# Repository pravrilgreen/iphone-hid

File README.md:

# iphone-hid

**Remote touch, keyboard and screen for real iPhones.** One small box per phone. People use it from
a browser; test frameworks use its HTTP API or the Python SDK.

**Demo videos:** [the console through every state](docs/media/console-demo.mp4) (2 min: touch, typing, the
phone's buttons, a test script running, the cable unplugged, the phone asleep, the picture lost, a
second operator, the box going away) and [on a phone](docs/media/console-demo-mobile.mp4) (20 s).
Recorded against the simulated iPhone with `make demo`.

## What it does

- **Live screen** in the browser, cut to the phone, at the phone's frame rate.
- **Touch as it happens.** Click to tap, drag to swipe or move things, scroll with the wheel, hold for
  a long press. The box drives the iPhone's absolute pointer, so every touch lands where it was made.
- **Keyboard.** Type straight onto the phone, or paste text (printable ASCII).
- **Phone buttons.** Home, App Switcher, Search, volume, mute, play/pause, and wake.
- **Automation.** A REST API with an OpenAPI description, a WebSocket for live control, a Python SDK
  and the `ihc` command. Boxes announce themselves on the local network.
- **One file to install.** A 3.4 MB self-installing bundle for ARM64 boards.

## How it works

- **Touch and keys.** The board's USB-C port runs as a USB device: an absolute pointer whose range
  covers the whole screen, a keyboard, and media keys. iOS shows the pointer through AssistiveTouch.
  The box sends each report as soon as the input arrives. While a report waits for the iPhone to
  collect it, newer moves replace the waiting one, so the pointer follows the hand without a queue;
  presses and releases always keep their order.
- **Screen.** The iPhone mirrors its screen over HDMI into the board's HDMI input. The box cuts the
  phone out of each 1080p frame, encodes it as JPEG with libjpeg-turbo, and sends it to each viewer
  as soon as the viewer has drawn the previous one.
- **Software.** `ihcd`, one static Go binary: the API, the console, the USB gadget set-up and the
  video capture.

## Performance

| Path | Measured | Where |
|---|---|---|
| Touch on the box: from the input arriving to its report queued on the USB port | under 0.1 ms typical, 0.3 ms at worst | `ihcd`, simulated iPhone, development machine |
| The iPhone collecting a queued report | 2.6 ms | Orange Pi 5 Plus and iPhone 15, earlier box software |
| JPEG encoding of the phone screen (498 × 1080) | 3.0 ms per frame | development machine (x86-64); not yet measured on the board |

A scripted tap takes about 260 ms by design: the pointer settles for 80 ms after a jump, the press
lasts 80 ms, then the releases. The picture runs at the iPhone's mirror rate, up to 60 fps with the
box's 1080p60 EDID; the glass-to-glass video latency on the board is not measured yet. On each box,
the console's top bar shows the touch latency, the picture rate and age, and the network round trip,
live.

## Status

- **On a real iPhone:** the box's USB gadget and its absolute pointer were confirmed on an iPhone 15
  with the earlier box software (iOS version not recorded). `ihcd` sets up the same gadget; its run
  through the [hardware check](docs/guide/hardware-check.md) on a board is pending, and its results
  will be published in `docs/test-logs/`.
- **Everything else** (the console, the API, the SDK, the touch engine, the fault states) is tested
  against the simulated iPhone, in CI and in the demo videos.
- **Pre-release:** versions 0.x are pre-releases, not yet tested as a whole on real hardware; the
  API may still change before 1.0. Changes are listed in the [changelog](CHANGELOG.md).

## Limits

- One pointer: taps, drags, swipes, long presses and the wheel. No pinch or other multi-touch.
- Typing takes printable ASCII on the U.S. hardware keyboard layout; other text is refused, not
  mistyped.
- The AssistiveTouch pointer shows on the screen, and so in screenshots.
- Apps that protect their content (DRM video) show black over HDMI.
- The box works as a person with a mouse and keyboard would: it does not install apps, read logs or
  inspect the UI tree.

## Security

- Every call except `/api/health` needs the box's token, a random string in `/var/lib/ihc/token`
  that only the service can read. WebSockets and image URLs pass it as `?token=`.
- The box serves plain HTTP on port 8000 of every interface. Keep boxes on a network of their own,
  or serve HTTPS (`--tls-cert`, `--tls-key`) and bind one interface (`--addr`): see
  [install](docs/guide/install.md#network-and-security).
- Pages of other origins are refused, and so are host names the box does not know (DNS names need
  `--allow-host`).
- Whoever has the token drives the phone like a person holding it; with the phone's passcode off,
  guard the token like the phone. Report vulnerabilities as [SECURITY.md](SECURITY.md) says.

## What each box needs

| Part | Notes |
|---|---|
| Orange Pi 5 Plus and its 5 V / 4 A supply | Runs the box: USB device port, HDMI input, network |
| USB-C hub with HDMI, USB-A and a USB-C PD charging input | HDMI through DisplayPort Alt Mode, e.g. UGREEN Revodok 105 (15495) |
| USB-C charger, 30 W or more | Into the hub's PD input: powers the hub, charges the phone |
| HDMI cable | Hub to the board's HDMI IN |
| USB-A to USB-C cable (data) | Hub's USB-A to the board's Type-C USB 3 port |
| Ethernet | API and console |

Phones: iPhone 15 and later with USB-C, except iPhone 16e, iPhone 17e and iPhone Air, which have no
video output. Each box drives one phone; a lab runs one box per phone.

![Wiring, step by step: 1 the iPhone into the hub, 2 a charger into the hub's power input, 3 the hub's HDMI into the board's HDMI IN, 4 the hub's USB-A into the board's Type-C port, 5 the board's power, 6 Ethernet. The picture flows from the iPhone to the network, touch and keys back, power from the charger.](box/web/guide/hub.svg)

## Install

1. Download `ihc-box-<version>-linux-arm64.run` from the newest of the
   [releases](https://github.com/pravrilgreen/iphone-hid/releases) (0.x releases are pre-releases) and
   copy it to the board.
2. `sudo sh ihc-box-*-linux-arm64.run`. It installs `ihcd`, the USB gadget and the service, and
   starts them. The API token is in `/var/lib/ihc/token`.
3. Open `http://<board address>:8000`.

`sudo ihcd doctor` examines the board and the box, part by part, and says how to fix each problem;
`--fix-safe` fixes what it can without cutting anything else off (the installer runs it), `--fix`
also what might. The [install guide](docs/guide/install.md) covers the board image, the HDMI input
and troubleshooting.

## Set up the iPhone

Once per phone: AssistiveTouch on, the pointer never hidden, Auto-Lock set to Never, the wired
accessory allowed, the U.S. hardware keyboard layout, and the middle pointer button mapped to App
Switcher. Step by step: [iPhone setup](docs/guide/iphone-setup.md). The
[hardware check](docs/guide/hardware-check.md) tries every button on the real phone.

## Use it

**In the browser.** Hover moves the phone's pointer; click taps; drag swipes, scrolls lists or moves
icons; the wheel scrolls. Click the screen, then type: the keyboard goes to the phone, and
Cmd/Ctrl+V types the clipboard. The volume keys and the side button on the drawn phone press the
real ones; Home, App Switcher and Search sit under it. The guide button (top right) shows these
drawings in the console, and the box's own state on the wiring: a cable at fault blinks, with what
to check.

**From code.**

```python
from ihc import Farm

phone = Farm.discover().devices()[0]        # or Farm("http://box.local:8000", token="...")
phone.tap(0.5, 0.93)                         # fractions of the screen: (0, 0) top left
phone.swipe(0.5, 0.8, 0.5, 0.2)
phone.drag(0.2, 0.3, 0.7, 0.3)
phone.type("hello\n")
phone.home()
phone.screenshot("screen.png")
```

```sh
curl -H "Authorization: Bearer $TOKEN" -H "Content-Type: application/json" \
     -d '{"x": 0.5, "y": 0.93}' http://box.local:8000/api/devices/iphone-b40d9e/tap
```

`pip install "iphone-hid[discovery] @ git+https://github.com/pravrilgreen/iphone-hid"` installs the
SDK and the `ihc` command (it is not on PyPI). The API is described
at `/api/openapi.json` on every box and in the [API reference](docs/dev/api.md).

## Roadmap

| Stage | Status |
|---|---|
| Orange Pi 5 Plus box: touch, keyboard, buttons, screen, API, console | Software done and tested against the simulated iPhone; the absolute pointer confirmed on an iPhone 15; the hardware check of `ihcd` pending |
| Purpose-built box: the iPhone's USB-C straight into an LT7911D bridge, a CH32V305 USB controller, an RV1106 SoC running `ihcd` ([how it is wired](box/web/guide/box.svg)) | Schematic designed to pin level and a draft 4-layer layout: [hardware/box-v1](hardware/box-v1/README.md) (KiCad, sheets, BOM, checks); the LT7911D pins and their routing wait for its datasheet to be copied in. Study: [custom box](docs/research/custom-box.md) |

## Repository

| Path | What |
|---|---|
| `box/` | `ihcd`, the box software (Go): touch engine, USB gadget, video, API, console (`box/web`), simulated iPhone |
| `src/ihc/` | Python SDK and the `ihc` command |
| `packaging/` | systemd units, udev rules, installer, bundle header |
| `hardware/box-v1/` | The purpose-built box: netlist as code, KiCad schematic and draft layout (generated), BOM, design checks |
| `scripts/` | bundle build and smoke test, diagrams, demo recording |
| `docs/` | guides, API, architecture, research ([index](docs/README.md)), demo videos (`docs/media`) |

## Development

```sh
make dev          # Python SDK in .venv with the test tools
make sim          # the box with a simulated iPhone on http://localhost:8000
make test         # gofmt, go vet, the Go tests, the SDK tests against a simulated box
make box          # dist/ihc-box-<version>-linux-arm64.run (Go, cmake, zig 0.13)
make check-box    # smoke-test the bundle (under qemu-aarch64 elsewhere)
make demo         # record docs/media/console-demo*.mp4 against a simulated box (pip install -e ".[demo]")
```

Changes are listed in the [changelog](CHANGELOG.md).

## License

[Apache License 2.0](LICENSE), for the software and the hardware design files alike. The box
binary also carries third-party components under their own licences: [box/THIRD_PARTY.md](box/THIRD_PARTY.md).

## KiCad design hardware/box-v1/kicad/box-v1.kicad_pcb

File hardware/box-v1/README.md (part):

# Box v1 (Option B): schematic design

> **Ordering the box?** Start with [ORDERING.md](ORDERING.md): the cover sheet for a PCB layout, fabrication and
> assembly house (package contents, what is complete, the blocking LT7911D item, fabrication and assembly
> specification, mechanical drawing, acceptance tests, cost estimate, RFQ email). This README is the engineering
> reference behind it.

- **Date:** 2026-09-26. **Status:** pin-level schematic and a **draft PCB layout** (every part placed, routed
  except the LT7911D area and 7 small places listed in §15, no DRC errors). Architecture and parts come from
  [custom-box.md](../../docs/research/custom-box.md) §4–§9 and §13.
- **Scope:** one 4-layer PCB of 96×66 mm with the LT7911D (USB-C DP Alt Mode → MIPI CSI-2), the CH32V305RBT6
  (USB High-Speed HID to the iPhone), a Luckfox Core1106 module (RV1106G3), USB-C PD power input, 100M RJ45, USB-C to
  the PC, debug headers, status LEDs and buttons.
- **Labels** (as in custom-box.md): **[Confirmed]** = read from the primary source (datasheet, vendor schematic,
  source code). **[Likely]** = vendor claim, indirect source (search excerpt, KiCad library) or a calculated value
  to be checked against the full datasheet. **[Unknown]** = no public data, must be measured or asked of the
  vendor. Net names, reference designators and pin names are in English.
- **Single source of truth:** [`netlist.py`](netlist.py). Every other file (KiCad, SVG, BOM, netlists, the pin
  tables in this README, the generated tables in ORDERING.md) is generated from it. To change the circuit or a
  part, edit `netlist.py`, then run `generate.py` and `check.py` again. The board is generated from the same
  netlist and from [`placement.py`](placement.py) by [`pcb.py`](pcb.py) (§15).
- **References and licences:** only vendor datasheets and reference designs (WCH, Luckfox, Rockchip), the official
  KiCad symbol library (to cross-check pinouts) and the Rockchip BSP Linux driver (device-tree property names
  only, no code copied). No schematic or file was copied from open hardware projects under GPL/AGPL (JetKVM,
  Luckfox PicoKVM, Aiden, the LT7911D projects on OSHWHub); these projects are not used as a pin source.

---

## 0. Summary

1. **The circuit is closed at pin level** for every part with a public datasheet: CH32V305RBT6, CH224K, Core1106,
   the regulators, ESD, connectors. `check.py` reports PASS: every pin is on a net or marked no-connect, every net
   has at least two pins, every IC power pin has a decoupling capacitor, no net names collide, and every part has
   ordering data. The connectivity read back from the KiCad files matches `netlist.py` on all 759 pins (see §13).
2. **The LT7911D is the biggest blind spot.** Its datasheet R1.4 turns out to be public (LCSC publishes it for part
   C5310990), but the build environment's network could not open it, so pins 1–23 still have numbers from public
   excerpts of the product brief **[Likely]** and the other 25 pins are drawn by function only, with placeholder
   numbers such as `?XTALI` **[Unknown]**. The layout places it with a provisional footprint and leaves its pins,
   the DP lanes and the CSI-2 lanes unrouted until the pin table is filled in (§15). Whether it can act as the power
   source for the iPhone is a firmware question for Lontium (§10.1). No other part does its job with public
   documentation: the other USB-C DP Alt Mode receivers (ITE, Realtek, Parade) are documented under NDA only, and
   so are Lontium's reference designs and firmware.
3. **Power:** the CH224K requests **9 V** from the PD charger (the block diagram says 12 V, reason in §3.1). Two
   LMR33630 bucks make 5.2 V/3 A for the iPhone and 5.0 V/3 A for the system; two TLV62569 bucks make 3.3 V and
   1.2 V. The iPhone gets VBUS through two back-to-back P-MOSFETs with a current shunt.
4. **Two ways to charge the iPhone**, chosen by fitting parts, not by redrawing the circuit:
   - **A (default):** the box supplies 5.2 V to the iPhone itself; the CH32V305 switches VBUS on.
   - **B (if the LT7911D supports dual-CC pass-through):** the charger's CC goes to the LT7911D, the charger's VBUS
     goes straight to the iPhone, and the LT7911D switches it on.
5. **A PD charger of ≥ 30 W** (9 V/3 A) is needed to charge the iPhone at 15 W and run the box (estimate in §3.5).
6. **Bill of materials:** every orderable line has a manufacturer and MPN; LCSC codes are given where they could be
   found, all marked **[Likely]** because lcsc.com and jlcpcb.com could not be opened from the build environment
   (§12). Design-review findings of 2026-09-26 are in §14.
7. **Layout (draft):** 96×66 mm, 4 layers, all SMD parts on the top. The iPhone port is on the front edge; Ethernet,
   the PC port and the power input on the rear. `pcb.py` places every part, routes with Freerouting and fills the
   copper zones. KiCad's DRC finds no clearance, hole or edge error; besides the LT7911D connections left open on
   purpose, 8 connections in 7 places are left for the person finishing the layout (§15).

---

## 1. Files in this directory

| File | Content |
|---|---|
| `ORDERING.md` | Cover sheet of the order package for a layout + fabrication + assembly house |
| `netlist.py` | Source of truth: parts (ref, value, footprint), every pin, nets, confidence, cited sources, and the `BUY` catalogue (manufacturer, MPN, LCSC code, evidence, JLCPCB class, price estimate, assembly class) |
| `layout.py` | Placement of the symbols on each sheet, shared by KiCad and SVG |
| `placement.py` | Where every big part sits on the board (connectors, ICs, inductors), the board size, holes, fiducials and the routing corridors kept free; shared by `pcb.py` and `mechanical.py` |
| `pcb.py` | Generates the board `kicad/box-v1.kicad_pcb` from `netlist.py` + `placement.py`: footprints, placement, rules, zones, routing through Freerouting, DRC (§15). Needs KiCad 7's `pcbnew` Python module |
| `footprints/box-v1.pretty/` | Footprints the KiCad library does not have (the HRO TYPE-C-31-M-04 receptacle); the LT7911D, Core1106 and CH224K footprints are built in `pcb.py` |
| `kicad/box-v1.kicad_pcb`, `kicad/drc.rpt` | The draft layout and its KiCad DRC report |
| `svg/pcb-*.svg` | Views of the layout: assembly (placement), each copper layer |
| `generate.py` | Writes `kicad/`, `svg/`, `bom.csv`, `netlist.json`, `kicad/box-v1.net`, the pin tables in this README and the generated tables in ORDERING.md; calls `mechanical.py` |
| `mechanical.py` | Enclosure outline and connector openings → `svg/mechanical.svg` and the openings table in ORDERING.md |
| `check.py` | Checks design rules and generated files; `--selftest` injects faults to prove that each rule catches them |
| `kicad/box-v1.kicad_pro`, `kicad/*.kicad_sch` | KiCad 8 project (format 20231120): root sheet + 5 sub-sheets |
| `kicad/box-v1.net` | KiCad netlist (s-expression, version E) with MPN, Manufacturer, LCSC and DNP fields |
| `svg/*.svg` | 5 schematic sheets viewable on GitHub, plus `svg/mechanical.svg` |
| `bom.csv` | Grouped BOM: reference, qty, value, manufacturer, mpn, lcsc, lcsc_confidence, lcsc_evidence, jlc_type, assembly, dnp, unit_price_usd_est, price_basis, footprint, confidence, notes (§12) |
| `netlist.json` | Parts (with ordering data), pins and nets as JSON |

Re-run after every change (standard Python 3 only):

```sh
cd hardware/box-v1
python3 generate.py            # regenerate every file
python3 check.py --selftest    # PASS/FAIL, non-zero exit code on errors
```

---

## 2. Block diagram

```
PD charger ─J101─ CH224K (9 V) ─ F101 ─ VIN ─┬─ U102 LMR33630 ─ 5V2_PHONE ─ JP101 ─ Q101/Q102 ─ R126 ─ PHONE_VBUS ─┐
                                             └─ U103 LMR33630 ─ 5V_SYS ─┬─ Core1106 (VCC5V0_SYS)                    │
                                                                       ├─ U104 TLV62569 ─ 3V3 ─ CH32V305, LT7911D IO  │
                                                                       └─ U105 TLV62569 ─ 1V2 ─ LT7911D (core, PHY)   │
iPhone ═J201 (USB-C 24P)═╦═ 4 SS pairs + SBU1/2 (DP Alt Mode) ─ U201 LT7911D ═ CSI-2 4 lanes ═ U401 Core1106     │
                         ╠═ CC1/CC2 ─ LT7911D (PD, Alt Mode) + CH32 ADC                                         │
                         ╠═ D+/D- ─ U301 CH32V305 (USB HS, HID)                                                  │
                         ╚═ VBUS ─────────────────────────────────────────────────────────────────────────────────┘
U301 CH32V305 ─ SPI0 + UART4 + IRQ/NRST/BOOT0 ─ U401 Core1106 ─┬─ FEPHY ─ J402 RJ45 (magjack)
                                                               ├─ USB OTG ─ J401 USB-C to the PC
                                                               └─ Wi-Fi 6 on the module (Wi-Fi variant, IPEX antenna connector)
```

Schematic sheets (generated, same content as the KiCad files):

| Sheet | SVG | KiCad |
|---|---|---|
| 1. Power | [svg/power.svg](svg/power.svg) | `kicad/power.kicad_sch` |
| 2. iPhone USB-C + LT7911D | [svg/iphone.svg](svg/iphone.svg) | `kicad/iphone.kicad_sch` |
| 3. CH32V305 | [svg/mcu.svg](svg/mcu.svg) | `kicad/mcu.kicad_sch` |
| 4. Core1106 + Ethernet + PC USB-C | [svg/soc.svg](svg/soc.svg) | `kicad/soc.kicad_sch` |
| 5. Debug, LEDs, buttons | [svg/debug.svg](svg/debug.svg) | `kicad/debug.kicad_sch` |
| Enclosure and openings (proposal) | [svg/mechanical.svg](svg/mechanical.svg) | - |

Drawing convention: no wires; every pin end carries a net label (global label) or a power symbol (rail), or a ×
(no connect). Two pins with the same label name are on the same net, also across sheets. In the SVGs, orange pin
names/numbers are **[Unknown]** and teal ones **[Likely]**; DNP parts are drawn dashed.

---

## 3. Power tree

### 3.1 USB-C PD input (J101, U101 CH224K)

- The CH224K is a PD sink configured by one resistor from CFG1 to GND: 6.8 kΩ = 9 V, 24 kΩ = 12 V, 56 kΩ = 15 V,
  open = 20 V. In resistor mode CFG2/CFG3 must stay open. **[Confirmed]**, CH224 datasheet §5.2.1.
- The circuit follows WCH's reference schematic §6.2: VDD from VIN through 1 kΩ with a 1 µF capacitor.
  **[Confirmed]** The CH224K's VBUS sense pin is left open: the datasheet allows it in PD-only mode (§5.5), and the
  pin is rated 13.5 V (§7.2), below VIN with a 15 V or 20 V profile. The first draft fed it from VIN through 10 kΩ.
- PD only: the CH224K DP and DM pins are shorted together, D+/D- of J101 are left open (datasheet §5.5). No QC/AFC
  protocol can therefore raise the voltage unexpectedly. **[Confirmed]**
- **9 V instead of the 12 V of the block diagram.** Every PD charger of 18 W or more has a fixed 9 V level; 12 V is
  not among the mandatory PD 3.0 levels, so many chargers lack it. **[Likely]** For 12 V, change R103 to 24 kΩ; the
  downstream circuit tolerates up to 20 V (LMR33630 36 V bucks, 50 V input capacitors).
- R101 (1 kΩ) is a 1206: it dissipates ~0.14 W at 15 V. A 20 V request (R103 open) would need 0.28 W, above its
  0.25 W rating, so the CH224K asks for 9–15 V only; Option B, which uses 20 V, removes U101 and R101 carries no
  current.
- **PG** (open drain, low = the requested voltage is present) is pulled up to 3V3 by R108 and goes to the
  CH32V305 (PB12). The MCU firmware only switches the iPhone VBUS on when PG is low.
- Input protection: F101 very fast 5 A/32 V fuse (1206), D101 SMBJ20A TVS (20 V standoff, 32.4 V clamp at 18.5 A,
  below the 36 V input rating of the LMR33630; the first draft's SMAJ24A clamped at 38.9 V), C101 47 µF 35 V to damp
  ringing when a long cable is hot-plugged. U107 (TPD4E05U06) protects the CC lines of J101 and J401 against ESD;
  the CH224K's CC pins are rated 8 V, so a cable that shorts CC to VBUS still needs a CC over-voltage switch
  (§8).

### 3.2 Rails

| Rail | Voltage | Source | Main loads | Design current | Notes |
|---|---|---|---|---|---|
| VBUS_IN / VIN | 9 V (5–20 V) | PD charger via J101, F101 | U102, U103, CH224K | ~2.8 A at 9 V | VIN is after the fuse |
| 5V2_PHONE | 5.22 V | U102 LMR33630ADDA, 400 kHz | iPhone through the switch | 3 A | R109/R110 = 100k/23.7k; on when VIN > ~7.2 V |
| 5V_SYS | 5.02 V | U103 LMR33630ADDA | Core1106, U104, U105 | 1.5 A (3 A rated) | R113/R114 = 100k/24.9k; on when VIN > ~4.3 V |
| 3V3 | 3.315 V | U104 TLV62569DBV, 1.5 MHz | CH32V305, LT7911D 3.3 V, pull-ups, LEDs, INA180 | ≤ 0.4 A (2 A rated) | R118/R119 = 100k/22.1k |
| 1V2 | 1.200 V | U105 TLV62569DBV | LT7911D 1.2 V | **[Unknown]**, 2 A budget | R121/R122 = 100k/100k; on after 3V3 |
| 3V3_LT | 3.3 V | FB201 from 3V3 | LT7911D 3.3 V pins | | ferrite 600 Ω@100 MHz |
| 1V2_LT_A | 1.2 V | FB202 from 1V2 | VCC12A_RX, VCC12_PI, VCC12_RXPLL | | isolates the PLL/analog supply |
| VDDA_MCU | 3.3 V | FB301 from 3V3 | CH32V305 VDDA | | datasheet: VDDA must equal VIO |
| CH224_VDD | 3.3 V | CH224K internal shunt | CH224K | a few mA | |
| PHONE_VBUS | 0 or 5.2 V | switch Q101/Q102 | iPhone | 3 A | discharged to 0 V through R210 |
| VCC_1V8_MOD, VCC_3V3_MOD | 1.8 / 3.3 V | PMIC on the Core1106 | RECOVERY key pull-up; TP | ≤ 300 mA per rail | per the Luckfox power table |

The VREF values (LMR33630: 1.0 V; TLV62569: 0.6 V) and the EN threshold (~1.2 V) are **[Likely]**: taken from the
library/memory, the TI datasheets could not be read in this environment. `check.py` (rule R10) recomputes the
output voltages, UVLO thresholds and ADC ranges from the resistor values in `netlist.py`; change VREF in
`check.py` if the datasheet differs.

Buck parts (each LMR33630): 2 × 10 µF 50 V X7R 1206 + 100 nF 50 V next to VIN/GND; 100 nF bootstrap capacitor;
1 µF VCC capacitor; 10 µH inductor (Isat ≥ 5 A for U102, ≥ 4 A for U103, 10×10 mm; the ordered Bourns SRP1038A-100M
is rated 7.5 A with ~30 mΩ DCR per the LCSC excerpt, against the original ≤ 25 mΩ target: ~0.27 W copper loss at
3 A); 3 × 22 µF 25 V X5R 1206 at the output. With 9 V → 5.2 V, 400 kHz and 10 µH the ripple current is ~0.55 A
(18 % of 3 A). Each TLV62569: 10 µF + 100 nF at the input, 2.2 µH inductor (Isat ≥ 3 A, 4×4 mm; the ordered
SRN4018-2R2M is rated 2.9 A per the LCSC excerpt, enough for the 2 A converter, confirm Isat on the datasheet),
2 × 22 µF 25 V X5R 0805 at the output.

### 3.3 Power-up sequence

1. VIN rises → U103 (5V_SYS) runs when VIN > ~4.3 V; U102 (5V2_PHONE) only runs when VIN > ~7.2 V, so with a non-PD
   (5 V) charger the box runs but does not charge the iPhone.
2. 5V_SYS → the Core1106 sequences its own rails with the EA3036C PMIC on the module **[Confirmed]** (Core1106
   schematic); U104 (3V3) starts immediately (EN pulled up to 5V_SYS).
3. U105 (1V2) starts about 4 ms after 3V3: its EN comes from 3V3 through a 100 kΩ/100 nF RC. 3.3 V before 1.2 V is a
   safe assumption; the real LT7911D requirement is **[Unknown]**.
4. LT7911D: RST_N is pulled up to 3V3 by 10 kΩ with a 1 µF capacitor (τ = 10 ms), so the chip runs as soon as it is
   powered and can handle PD/CC. The RV1106 controls the reset through GPIO0_A3 (pad 61); this pin defaults to a
   pull-up, so it does not hold the LT7911D in reset while the SoC boots. **[Confirmed]** for the default level
   (`_u` suffix in the Luckfox pin table).
5. The CH32V305 has an internal POR; NRST has a 4.7 kΩ/100 nF RC.
6. CSI path: the LT7911D may drive LP-11 before the RV1106 has booted. Both come up from the same 5V_SYS within a few
   ms; the driver opens the stream only after probing. The risk of back-feeding through the CSI pins while the
   module is unpowered is low but **[Unknown]**.

### 3.4 Charging path to the iPhone (pass-through)

Switch: Q101 and Q102 (SO-8 P-MOSFETs, AO4407A: −30 V, ~11 mΩ at Vgs −10 V and about 18 mΩ at −4.5 V **[Likely]**)
share their sources (PSW_S), with the drains facing outwards. When off, the two body diodes block both directions,
so the iPhone cannot feed back into the box and the box cannot push voltage out before it is allowed to. Q103
(2N7002) pulls the gate down through R124 10 kΩ; R123 100 kΩ holds the gate off; C128 47 nF gives a ~0.5 ms soft
start; D102 (10 V zener) clamps Vgs in Option B with VIN up to 20 V. At 5.2 V, Vgs ≈ −4.7 V.

| | Option A (default) | Option B |
|---|---|---|
| Charger CC (J101) | to the CH224K (R104/R105 = 0 Ω) | to the second PD port of the LT7911D (R106/R107 = 0 Ω, remove R104/R105, remove U101) |
| Switch supply | 5V2_PHONE (JP101 bridged 1-2) | VIN (JP101 bridged 2-3), voltage negotiated by the LT7911D |
| Who switches | CH32V305 PB1 (R127 = 0 Ω) | LT7911D GPIO (R128 = 0 Ω, remove R127) |
| TVS on the iPhone VBUS | D201 SMF6.0A | change to SMF22A |
| Condition | LT7911D can act as Source (Rp) + UFP_D + DR_Swap with the iPhone | LT7911D has dual-CC pass-through firmware |

VBUS enable logic in the MCU firmware (Option A): PD_PG low **and** iPhone-side VBUS < 0.8 V (nobody else is
supplying it) **and** the CC1/CC2 voltages show an Rd device. Switch off when the current (PHONE_ISENSE) exceeds
the limit or when the cable is unplugged. The MCU reads CC1_SENSE/CC2_SENSE (through 100 kΩ, no load on the CC
lines), PHONE_VBUS_SENSE (100k/15k divider, 20 V → 2.6 V) and PHONE_ISENSE (INA180A2, gain 50, 10 mΩ shunt →
0.5 V/A, up to 6.6 A before saturating at 3.3 V).

Per the Type-C specification, a source must bring VBUS back to vSafe0V (< 0.8 V) after unplugging; R210 10 kΩ with
~20 µF in total takes 5.2 V down to 0.8 V in ~0.4 s (limit 650 ms). **[Likely]**, per the USB Type-C spec.

### 3.5 Power estimate

| Load | Power | Confidence |
|---|---|---|
| iPhone, 5.2 V × 3 A | 15.6 W | [Likely]: the iPhone draws up to 3 A when the source advertises 3 A |
| Core1106 | 2.4 W measured (467 mA), 5 W (1 A) design | [Confirmed], Luckfox power table |
| 3V3 (CH32V305, LT7911D 3.3 V, LEDs) | ≤ 1.3 W | [Unknown] for the LT7911D |
| 1V2 (LT7911D) | ≤ 1 W | [Unknown] |
| Total from VIN (buck efficiency ~92 %) | ~25 W → ~2.8 A at 9 V | estimate |

Conclusion: a PD charger with a 9 V/3 A level (30 W class) is needed. With a 20 W charger the firmware should limit
the iPhone current (switch off when PHONE_ISENSE is high or VIN_SENSE sags).

### 3.6 Powering the box from the PC (JP102, development only)

JP102 is open by default. With JP102 bridged, PC_VBUS → D104 (SS34) → 5V_SYS gives ~4.6–4.7 V, right at the 4.6 V
minimum of the Core1106. **Do not plug a charger into J101 while JP102 is bridged:** 5V_SYS could then flow
backwards through the body diode of U103 to VIN and out of the J101 VBUS pin. The iPhone is not charged in this
mode (U102 off).

---

## 4. Blocks and pin tables

Every table below is generated from `netlist.py`. The "Connects to" column lists the other pins on the same net
(`REF.pin`). NC = no connect (no-connect flag in KiCad). The last column is the confidence of the **pin number and
function**. The header line of each part names the ordered part (manufacturer and MPN, see §12).

### 4.1 Power

Sources: CH224K per the WCH datasheet (V1F copy on GitHub); LMR33630, TLV62569, INA180A2, AO4407A/2N7002 per the
KiCad 8.0.9 symbol library (which copies the vendors' pinouts) **[Likely]**; the USB-C connectors per the standard
Type-C pinout **[Confirmed]**. CH224K CC1/CC2: the datasheet pin table says "6, 7 = CC1, CC2" but figure §6.2 and
the KiCad symbol say CC1 = 7, CC2 = 6; both pins are symmetric so either way works, the schematic follows figure
§6.2.

<!-- BEGIN GENERATED: pins-power -->
**J101 USB-C PD IN** (Korean Hroparts Elec TYPE-C-31-M-12; footprint `Connector_USB:USB_C_Receptacle_HRO_TYPE-C-31-M-12`; source: [KICAD_SYM](https://gitlab.com/kicad/libraries/kicad-symbols/-/tree/8.0.9))

| Pin | Name | Net | Connects to | Note | Confidence |
|---|---|---|---|---|---|
| A1 | GND | GND | rail (161 pins) |  | [Confirmed] |
| A4 | VBUS | VBUS_IN | F101.1 |  | [Confirmed] |
| A5 | CC1 | PD_CC1 | R104.1, R106.1, U107.1 |  | [Confirmed] |
| A6 | D+ | NC | - |  | [Confirmed] |
| A7 | D- | NC | - |  | [Confirmed] |
| A8 | SBU1 | NC | - |  | [Confirmed] |
| A9 | VBUS | VBUS_IN | F101.1 |  | [Confirmed] |
| A12 | GND | GND | rail (161 pins) |  | [Confirmed] |
| B1 | GND | GND | rail (161 pins) |  | [Confirmed] |
| B4 | VBUS | VBUS_IN | F101.1 |  | [Confirmed] |
| B5 | CC2 | PD_CC2 | R105.1, R107.1, U107.2 |  | [Confirmed] |
| B6 | D+ | NC | - |  | [Confirmed] |
| B7 | D- | NC | - |  | [Confirmed] |
| B8 | SBU2 | NC | - |  | [Confirmed] |
| B9 | VBUS | VBUS_IN | F101.1 |  | [Confirmed] |
| B12 | GND | GND | rail (161 pins) |  | [Confirmed] |
| S1 | SHIELD | GND | rail (161 pins) |  | [Confirmed] |

**JP101 PSW_SRC** (-; footprint `Jumper:SolderJumper-3_P1.3mm_Bridged12_RoundedPad1.0x1.5mm`; source: -)

| Pin | Name | Net | Connects to | Note | Confidence |
|---|---|---|---|---|---|
| 1 | A | 5V2_PHONE | L101.2, C108.1, C109.1, C110.1, R109.1, TP502.1 |  | [Confirmed] |
| 2 | C | PSW_IN | Q101.5, Q101.6, Q101.7, Q101.8 |  | [Confirmed] |
| 3 | B | VIN | rail (16 pins) |  | [Confirmed] |

**JP102 PC_PWR** (-; footprint `Jumper:SolderJumper-2_P1.3mm_Open_RoundedPad1.0x1.5mm`; source: -)

| Pin | Name | Net | Connects to | Note | Confidence |
|---|---|---|---|---|---|
| 1 | A | PC_VBUS | rail (7 pins) |  | [Confirmed] |
| 2 | B | PCPWR_A | D104.2 |  | [Confirmed] |

**Q101 AO4407A** (Alpha & Omega Semiconductor AO4407A; footprint `Package_SO:SOIC-8_3.9x4.9mm_P1.27mm`; source: [KICAD_SYM](https://gitlab.com/kicad/libraries/kicad-symbols/-/tree/8.0.9))

| Pin | Name | Net | Connects to | Note | Confidence |
|---|---|---|---|---|---|
| 1 | S | PSW_S | Q102.1, Q102.2, Q102.3, R123.1, C128.1, D102.1 |  | [Confirmed] |
| 2 | S | PSW_S | Q102.1, Q102.2, Q102.3, R123.1, C128.1, D102.1 |  | [Confirmed] |
| 3 | S | PSW_S | Q102.1, Q102.2, Q102.3, R123.1, C128.1, D102.1 |  | [Confirmed] |
| 4 | G | PSW_G | Q102.4, R123.2, C128.2, D102.2, R124.1 |  | [Confirmed] |
| 5 | D | PSW_IN | JP101.2 |  | [Confirmed] |
| 6 | D | PSW_IN | JP101.2 |  | [Confirmed] |
| 7 | D | PSW_IN | JP101.2 |  | [Confirmed] |
| 8 | D | PSW_IN | JP101.2 |  | [Confirmed] |

**Q102 AO4407A** (Alpha & Omega Semiconductor AO4407A; footprint `Package_SO:SOIC-8_3.9x4.9mm_P1.27mm`; source: [KICAD_SYM](https://gitlab.com/kicad/libraries/kicad-symbols/-/tree/8.0.9))

| Pin | Name | Net | Connects to | Note | Confidence |
|---|---|---|---|---|---|
| 1 | S | PSW_S | Q101.1, Q101.2, Q101.3, R123.1, C128.1, D102.1 |  | [Confirmed] |
| 2 | S | PSW_S | Q101.1, Q101.2, Q101.3, R123.1, C128.1, D102.1 |  | [Confirmed] |
| 3 | S | PSW_S | Q101.1, Q101.2, Q101.3, R123.1, C128.1, D102.1 |  | [Confirmed] |
| 4 | G | PSW_G | Q101.4, R123.2, C128.2, D102.2, R124.1 |  | [Confirmed] |
| 5 | D | PSW_OUT | R126.1, U106.3 |  | [Confirmed] |
| 6 | D | PSW_OUT | R126.1, U106.3 |  | [Confirmed] |
| 7 | D | PSW_OUT | R126.1, U106.3 |  | [Confirmed] |
| 8 | D | PSW_OUT | R126.1, U106.3 |  | [Confirmed] |

**Q103 2N7002** (Changjiang Electronics Tech (CJ) 2N7002; footprint `Package_TO_SOT_SMD:SOT-23`; source: [KICAD_SYM](https://gitlab.com/kicad/libraries/kicad-symbols/-/tree/8.0.9))

| Pin | Name | Net | Connects to | Note | Confidence |
|---|---|---|---|---|---|
| 1 | G | PHONE_VBUS_EN | R125.1, R127.2, R128.2 |  | [Confirmed] |
| 2 | S | GND | rail (165 pins) |  | [Confirmed] |
| 3 | D | PSW_GD | R124.2 |  | [Confirmed] |

**U101 CH224K** (WCH (Jiangsu Qin Heng) CH224K; footprint `Package_SO:SSOP-10-1EP_3.9x4.9mm_P1mm_EP2.1x3.3mm`; source: [CH224](https://raw.githubusercontent.com/makespacemadrid/cheap-wled-controller/main/datasheet/ch224k.pdf))

| Pin | Name | Net | Connects to | Note | Confidence |
|---|---|---|---|---|---|
| 1 | VDD | CH224_VDD | R101.2, C102.1 | internal 3.3 V shunt, fed from VIN through 1 kΩ | [Confirmed] |
| 2 | CFG2 | NC | - | resistor mode: CFG2/CFG3 must stay open (§5.2.1) | [Confirmed] |
| 3 | CFG3 | NC | - | same as CFG2 | [Confirmed] |
| 4 | DP | CH224_DPDM |  | DP-DM shorted: PD only (§5.5) | [Confirmed] |
| 5 | DM | CH224_DPDM |  | DP-DM shorted | [Confirmed] |
| 6 | CC2 | CH224_CC2 | R105.2 | through R105 0R to J101.B5 | [Confirmed] |
| 7 | CC1 | CH224_CC1 | R104.2 | through R104 0R to J101.A5 | [Confirmed] |
| 8 | VBUS | NC | - | left open: PD-only mode allows it (§5.5), and the pin is rated 13.5 V, below VIN at 15-20 V | [Confirmed] |
| 9 | CFG1 | CH224_CFG1 | R103.1 | 6.8 kΩ to GND = request 9 V | [Confirmed] |
| 10 | PG | PD_PG | R108.1, U301.33 | open drain, low = requested voltage present | [Confirmed] |
| 11 | GND | GND | rail (165 pins) | EPAD (the datasheet calls it pin 0) | [Confirmed] |

**U102 LMR33630ADDA** (Texas Instruments LMR33630ADDAR; footprint `Package_SO:Texas_HSOP-8-1EP_3.9x4.9mm_P1.27mm_ThermalVias`; source: [KICAD_SYM](https://gitlab.com/kicad/libraries/kicad-symbols/-/tree/8.0.9))

| Pin | Name | Net | Connects to | Note | Confidence |
|---|---|---|---|---|---|
| 1 | GND | GND | rail (164 pins) |  | [Confirmed] |
| 2 | VIN | VIN | rail (16 pins) |  | [Confirmed] |
| 3 | EN | U102_EN | R111.2, R112.1 | UVLO divider 100k/20k | [Confirmed] |
| 4 | PG | NC | - | not used | [Confirmed] |
| 5 | FB | U102_FB | R109.2, R110.1 |  | [Confirmed] |
| 6 | VCC | U102_VCC | C106.1 | internal LDO, 1 µF capacitor | [Confirmed] |
| 7 | BOOT | U102_BOOT | C107.1 |  | [Confirmed] |
| 8 | SW | U102_SW | C107.2, L101.1 |  | [Confirmed] |
| 9 | EP | GND | rail (164 pins) | thermal pad = GND | [Confirmed] |

**U103 LMR33630ADDA** (Texas Instruments LMR33630ADDAR; footprint `Package_SO:Texas_HSOP-8-1EP_3.9x4.9mm_P1.27mm_ThermalVias`; source: [KICAD_SYM](https://gitlab.com/kicad/libraries/kicad-symbols/-/tree/8.0.9))

| Pin | Name | Net | Connects to | Note | Confidence |
|---|---|---|---|---|---|
| 1 | GND | GND | rail (164 pins) |  | [Confirmed] |
| 2 | VIN | VIN | rail (16 pins) |  | [Confirmed] |
| 3 | EN | U103_EN | R115.2, R116.1 | UVLO divider 100k/39k | [Confirmed] |
| 4 | PG | NC | - | not used | [Confirmed] |
| 5 | FB | U103_FB | R113.2, R114.1 |  | [Confirmed] |
| 6 | VCC | U103_VCC | C114.1 | internal LDO, 1 µF capacitor | [Confirmed] |
| 7 | BOOT | U103_BOOT | C115.1 |  | [Confirmed] |
| 8 | SW | U103_SW | C115.2, L102.1 |  | [Confirmed] |
| 9 | EP | GND | rail (164 pins) | thermal pad = GND | [Confirmed] |

**U104 TLV62569DBV** (Texas Instruments TLV62569DBVR; footprint `Package_TO_SOT_SMD:SOT-23-5`; source: [KICAD_SYM](https://gitlab.com/kicad/libraries/kicad-symbols/-/tree/8.0.9))

| Pin | Name | Net | Connects to | Note | Confidence |
|---|---|---|---|---|---|
| 1 | EN | U104_EN | R117.2 |  | [Confirmed] |
| 2 | GND | GND | rail (165 pins) |  | [Confirmed] |
| 3 | SW | U104_SW | L103.1 |  | [Confirmed] |
| 4 | VIN | 5V_SYS | rail (18 pins) |  | [Confirmed] |
| 5 | FB | U104_FB | R118.2, R119.1 |  | [Confirmed] |

**U105 TLV62569DBV** (Texas Instruments TLV62569DBVR; footprint `Package_TO_SOT_SMD:SOT-23-5`; source: [KICAD_SYM](https://gitlab.com/kicad/libraries/kicad-symbols/-/tree/8.0.9))

| Pin | Name | Net | Connects to | Note | Confidence |
|---|---|---|---|---|---|
| 1 | EN | U105_EN | R120.2, C125.1 |  | [Confirmed] |
| 2 | GND | GND | rail (165 pins) |  | [Confirmed] |
| 3 | SW | U105_SW | L104.1 |  | [Confirmed] |
| 4 | VIN | 5V_SYS | rail (18 pins) |  | [Confirmed] |
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
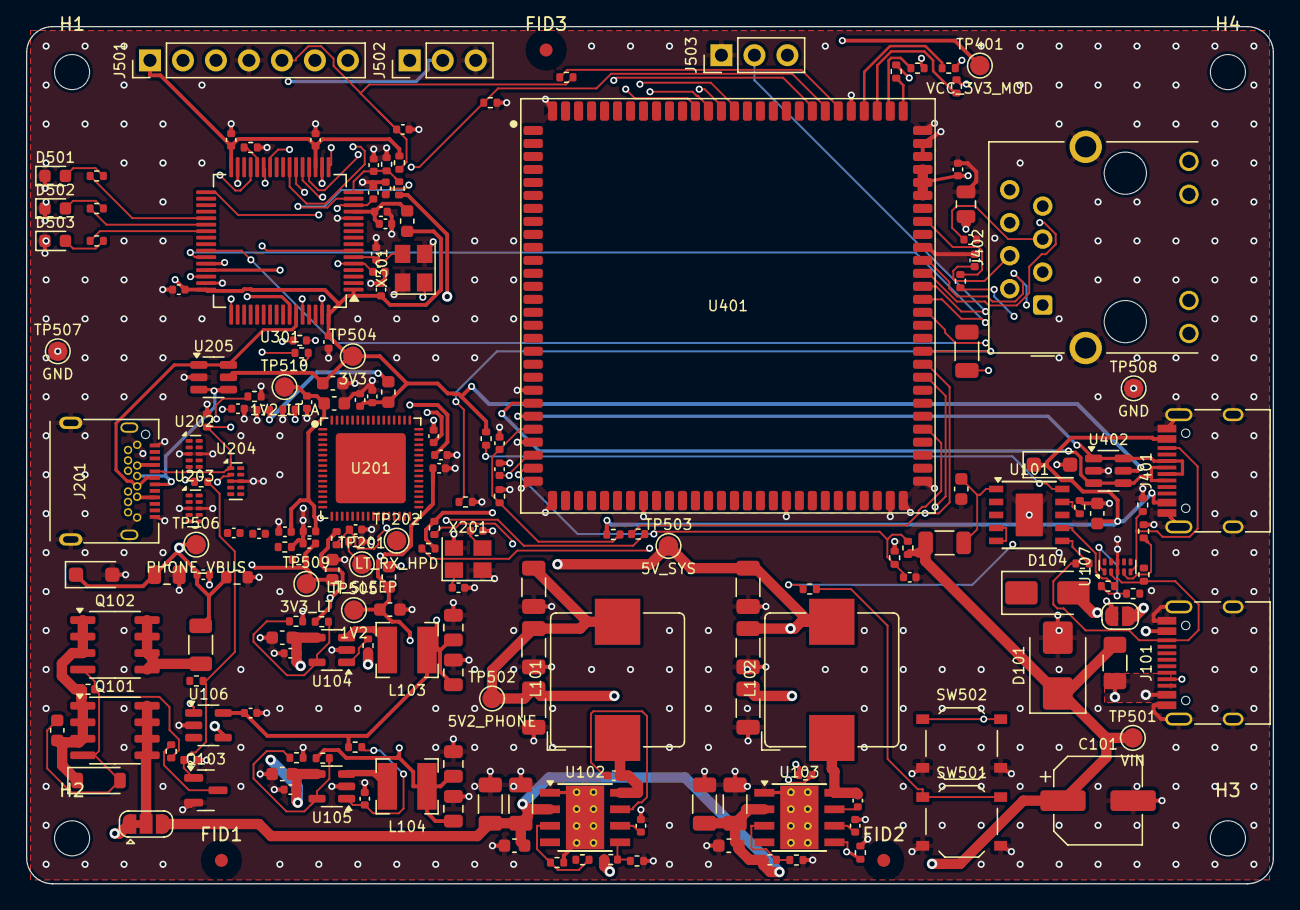
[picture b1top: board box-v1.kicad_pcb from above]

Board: 4 copper layers, 96.0 x 66.0 mm, 202 parts (0 on the bottom side), 122 nets.

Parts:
C101: 47uF 35V; CP_Elec_6.3x7.7
C102, C404: 1uF 50V; C_0603_1608Metric
C103, C104, C111, C112: 10uF 50V X7R; C_1206_3216Metric
C105, C113: 100nF 50V; C_0603_1608Metric
C106, C114, C309: 1uF 25V; C_0402_1005Metric
C107, C115: 100nF 16V; C_0402_1005Metric
C108, C109, C110, C116, C117, C118: 22uF 25V X5R; C_1206_3216Metric
C119, C123, C212, C213, C214, C310: 10uF 10V; C_0603_1608Metric
C120, C124, C125, C129, C203, C204, C205, C206, C207, C208, C209, C210, C211, C215, C216, C217, C218, C303, C304, C305, C306, C307, C308, C311, C402, C403, C405: 100nF; C_0402_1005Metric
C121, C122, C126, C127, C401: 22uF 25V X5R; C_0805_2012Metric
C128: 47nF 50V; C_0603_1608Metric
C130, C312, C313: 1nF; C_0402_1005Metric
C201, C202, C301, C302: 18pF C0G; C_0402_1005Metric
C219: 10uF 25V; C_0805_2012Metric
C220: 100nF 50V; C_0402_1005Metric
C314, C409: 10nF; C_0402_1005Metric
C406, C407: 10nF 50V; C_0402_1005Metric
C408: 1nF 2kV X7R; C_1206_3216Metric
C410: 1nF C0G; C_0402_1005Metric
D101: SMBJ20A; D_SMB
D102: BZT52C10; D_SOD-123
D104: SS34; D_SMA
D201, D401: SMF6.0A; D_SOD-123F
D501: RED; LED_0603_1608Metric
D502: YELLOW; LED_0603_1608Metric
D503: GREEN; LED_0603_1608Metric
F101: 5A 32V; Fuse_1206_3216Metric
FB201, FB202, FB301: 600R@100MHz; L_0603_1608Metric
FID1, FID2, FID3: Fiducial_1mm_Mask2mm
H1, H2, H3, H4: M2.5; MountingHole_2.7mm_M2.5
J101: USB-C PD IN; USB_C_Receptacle_HRO_TYPE-C-31-M-12
J201: USB-C iPhone; USB_C_Receptacle_HRO_TYPE-C-31-M-04
J401: USB-C PC; USB_C_Receptacle_HRO_TYPE-C-31-M-12
J402: RJ45 10/100; RJ45_Hanrun_HR911105A_Horizontal
J501: MCU SWD+UART; PinHeader_1x07_P2.54mm_Vertical
J502: MCU USB FS; PinHeader_1x03_P2.54mm_Vertical
J503: SoC UART; PinHeader_1x03_P2.54mm_Vertical
JP101: PSW_SRC; SolderJumper-3_P1.3mm_Bridged12_RoundedPad1.0x1.5mm
JP102: PC_PWR; SolderJumper-2_P1.3mm_Open_RoundedPad1.0x1.5mm
L101, L102: 10uH; L_Bourns_SRP1038C_10.0x10.0mm
L103, L104: 2.2uH; L_Bourns-SRN4018
Q101, Q102: AO4407A; SOIC-8_3.9x4.9mm_P1.27mm
Q103: 2N7002; SOT-23
R101: 1k; R_1206_3216Metric
R103: 6.8k 1%; R_0402_1005Metric
R104, R105, R106, R107, R127, R128, R405, R406, R407, R408: 0R; R_0402_1005Metric
R108, R124, R203, R204, R302, R303, R403, R411: 10k; R_0402_1005Metric
R109, R113, R118, R121, R122, R409: 100k 1%; R_0402_1005Metric
R110: 23.7k 1%; R_0402_1005Metric
R111, R115, R117, R120, R123, R125, R205, R304, R305, R306: 100k; R_0402_1005Metric
R112: 20k; R_0402_1005Metric
R114: 24.9k 1%; R_0402_1005Metric
R116: 39k; R_0402_1005Metric
R119: 22.1k 1%; R_0402_1005Metric
R126: 10m 1%; R_1206_3216Metric
R201, R202: 2.2k; R_0402_1005Metric
R206, R207: 1M; R_0402_1005Metric
R210: 10k; R_0603_1608Metric
R211, R212: 5.1k; R_0402_1005Metric
R213, R413: 1k; R_0402_1005Metric
R301: 4.7k; R_0402_1005Metric
R307: 15k; R_0402_1005Metric
R401, R402: 5.1k 1%; R_0402_1005Metric
R404: 18k; R_0402_1005Metric
R410: 8.2k 1%; R_0402_1005Metric
R412: 100R; R_0402_1005Metric
R501, R502: 680R; R_0402_1005Metric
R503: 560R; R_0402_1005Metric
SW501: RECOVERY; SW_Push_1P1T_XKB_TS-1187A
SW502: RESET; SW_Push_1P1T_XKB_TS-1187A
TP201: LT_SLEEP; TestPoint_Pad_D1.5mm
TP202: LT_RX_HPD; TestPoint_Pad_D1.5mm
TP401: VCC_3V3_MOD; TestPoint_Pad_D1.5mm
TP501: VIN; TestPoint_Pad_D1.5mm
TP502: 5V2_PHONE; TestPoint_Pad_D1.5mm
TP503: 5V_SYS; TestPoint_Pad_D1.5mm
TP504: 3V3; TestPoint_Pad_D1.5mm
TP505: 1V2; TestPoint_Pad_D1.5mm
TP506: PHONE_VBUS; TestPoint_Pad_D1.5mm
TP507, TP508: GND; TestPoint_Pad_D1.5mm
TP509: 3V3_LT; TestPoint_Pad_D1.5mm
TP510: 1V2_LT_A; TestPoint_Pad_D1.5mm
U101: CH224K; SSOP-10-1EP_3.9x4.9mm_P1mm_EP2.1x3.3mm
U102, U103: LMR33630ADDA; Texas_HSOP-8-1EP_3.9x4.9mm_P1.27mm_ThermalVias
U104, U105: TLV62569DBV; SOT-23-5
U106: INA180A2; SOT-23-5
U107, U202, U203, U204: TPD4E05U06DQA; USON-10_2.5x1.0mm_P0.5mm
U201: LT7911D; LT7911D_QFN-64-1EP_7.5x7.5mm_P0.4mm
U205, U402: USBLC6-2SC6; SOT-23-6
U301: CH32V305RBT6; LQFP-64_10x10mm_P0.5mm
U401: Luckfox Core1106; Luckfox_Core1106_Castellated_30x30mm_P1.0mm
X201: 25MHz; Crystal_SMD_3225-4Pin_3.2x2.5mm
X301: 8MHz; Crystal_SMD_3225-4Pin_3.2x2.5mm

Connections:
1V2: C126.1, C127.1, C203.1, C209.1, C211.1, C212.1, FB202.1, L104.2, R121.1, TP505.1, U201.1
1V2_LT_A: C204.1, C206.1, C207.1, C213.1, FB202.2, TP510.1, U201.4, U201.10, U201.13
3V3: C121.1, C122.1, C129.1, C218.1, C303.1, C304.1, C305.1, C306.1, C307.1, C310.1, C403.1, FB201.1, FB301.1, J501.1, L103.2, R108.2, R118.1, R120.1, R203.2, R301.2, TP504.1, U106.5, U205.5, U301.1, U301.19, U301.32, U301.48, U301.64, U402.5
3V3_LT: C205.1, C208.1, C210.1, C214.1, FB201.2, R207.2, TP509.1, U201.7, U201.16
5V2_PHONE: C108.1, C109.1, C110.1, JP101.1, L101.2, R109.1, TP502.1
5V_SYS: C116.1, C117.1, C118.1, C119.1, C120.1, C123.1, C124.1, C401.1, C402.1, D104.1, L102.2, R113.1, R117.1, TP503.1, U104.4, U105.4, U401.79, U401.80, U401.81
CC1_SENSE: C312.1, R304.2, U301.14
CC2_SENSE: C313.1, R305.2, U301.15
CH224_CC1: R104.2, U101.7
CH224_CC2: R105.2, U101.6
CH224_CFG1: R103.1, U101.9
CH224_DPDM: U101.4, U101.5
CH224_VDD: C102.1, R101.2, U101.1
ETH_BS: C408.1, J402.8
ETH_RCT: C407.1, J402.5
ETH_RXN_J: J402.6, R408.2
ETH_RXP_J: J402.3, R407.2
ETH_RX_N: R408.1, U401.85
ETH_RX_P: R407.1, U401.86
ETH_TCT: C406.1, J402.4
ETH_TXN_J: J402.2, R406.2
ETH_TXP_J: J402.1, R405.2
ETH_TX_N: R406.1, U401.87
ETH_TX_P: R405.1, U401.88
GND: C101.2, C102.2, C103.2, C104.2, C105.2, C106.2, C108.2, C109.2, C110.2, C111.2, C112.2, C113.2, C114.2, C116.2, C117.2, C118.2, C119.2, C120.2, C121.2, C122.2, C123.2, C124.2, C125.2, C126.2, C127.2, C129.2, C130.2, C201.2, C202.2, C203.2, C204.2, C205.2, C206.2, C207.2, C208.2, C209.2, C210.2, C211.2, C212.2, C213.2, C214.2, C215.2, C218.2, C219.2, C220.2, C301.2, C302.2, C303.2, C304.2, C305.2, C306.2, C307.2, C308.2, C309.2, C310.2, C311.2, C312.2, C313.2, C314.2, C401.2, C402.2, C403.2, C404.2, C405.2, C406.2, C407.2, C408.2, C409.2, C410.2, D101.2, D201.2, D401.2, D501.1, D502.1, D503.1, J101.A1, J101.A12, J101.B1, J101.B12, J101.S1, J201.31, J201.32, J201.33, J201.34, J201.A1, J201.A12, J201.B1, J201.B12, J401.A1, J401.A12, J401.B1, J401.B12, J401.S1, J402.SH, J501.4, J502.3, J503.1, Q103.2, R103.2, R110.2, R112.2, R114.2, R116.2, R119.2, R122.2, R125.2, R204.2, R205.2, R206.2, R210.2, R211.2, R212.2, R302.2, R303.2, R307.2, R401.2, R402.2, R404.2, R410.2, SW501.2, SW502.2, TP507.1, TP508.1, U101.11, U102.1, U102.9, U103.1, U103.9, U104.2, U105.2, U106.2, U107.3, U107.8, U202.3, U202.8, U203.3, U203.8, U204.3, U204.8, U205.2, U301.12, U301.18, U301.31, U301.47, U301.63, U401.21, U401.25, U401.28, U401.29, U401.36, U401.47, U401.55, U401.56, U401.57, U401.75, U401.82, U401.83, U401.84, U401.89, U401.112, U402.2, X201.2, X201.4, X301.2, X301.4
HSE_IN: C301.1, U301.5, X301.1
HSE_OUT: C302.1, U301.6, X301.3
LED_G: R503.1, U301.39
LED_G_A: D503.2, R503.2
LED_R: R501.1, U301.37
LED_R_A: D501.2, R501.2
LED_Y: R502.1, U301.38
LED_Y_A: D502.2, R502.2
LT_AUX_N: C217.2, R207.1, U201.18
LT_AUX_P: C216.2, R206.1, U201.17
LT_INT: R205.1, U401.67
LT_RST_N: C215.1, R203.1, R213.2, U201.20
LT_RX_HPD: TP202.1, U201.23
LT_SCL: R201.1, U201.21, U401.65
LT_SDA: R202.1, U201.22, U401.66
LT_SLEEP: R204.1, TP201.1, U201.19
LT_XI: C201.1, X201.1
LT_XO: C202.1, X201.3
MCU_BOOT0: R302.1, U301.60, U401.91
MCU_BOOT1: R303.1, U301.28
MCU_DBG_RX: J501.7, U301.30
MCU_DBG_TX: J501.6, U301.29
MCU_FS_DN: J502.2, U301.44
MCU_FS_DP: J502.1, U301.45
MCU_IRQ: U301.26, U401.92
MCU_NRST: C311.1, J501.5, R301.1, R413.2, U301.7
MCU_UART_RX: U301.43, U401.71
MCU_UART_TX: U301.42, U401.70
MCU_VBUS_EN: R127.1, U301.27
PCPWR_A: D104.2, JP102.2
PC_CC1: J401.A5, R401.1, U107.4
PC_CC2: J401.B5, R402.1, U107.5
PC_USB_DN: J401.A7, J401.B7, U401.22, U402.3, U402.4
PC_USB_DP: J401.A6, J401.B6, U401.23, U402.1, U402.6
PC_VBUS: C404.1, D401.1, J401.A4, J401.A9, J401.B4, J401.B9, JP102.1, R403.1
PC_VBUS_DET: C405.1, R403.2, R404.1, U401.24
PD_CC1: J101.A5, R104.1, R106.1, U107.1
PD_CC2: J101.B5, R105.1, R107.1, U107.2
PD_PG: R108.1, U101.10, U301.33
PHONE_CC1: J201.A5, R211.1, R304.1, U201.14, U204.1
PHONE_CC2: J201.B5, R212.1, R305.1, U201.15, U204.2
PHONE_ISENSE: C130.1, U106.1, U301.17
PHONE_SBU1: C216.1, J201.A8, U204.4
PHONE_SBU2: C217.1, J201.B8, U204.5
PHONE_USB_DN: J201.A7, J201.B7, U205.3, U205.4, U301.58
PHONE_USB_DP: J201.A6, J201.B6, U205.1, U205.6, U301.59
PHONE_VBUS: C219.1, C220.1, D201.1, J201.A4, J201.A9, J201.B4, J201.B9, R126.2, R210.1, R306.1, TP506.1, U106.4
PHONE_VBUS_EN: Q103.1, R125.1, R127.2, R128.2
PHONE_VBUS_SENSE: C314.1, R306.2, R307.1, U301.16
PSW_G: C128.2, D102.2, Q101.4, Q102.4, R123.2, R124.1
PSW_GD: Q103.3, R124.2
PSW_IN: JP101.2, Q101.5, Q101.6, Q101.7, Q101.8
PSW_OUT: Q102.5, Q102.6, Q102.7, Q102.8, R126.1, U106.3
PSW_S: C128.1, D102.1, Q101.1, Q101.2, Q101.3, Q102.1, Q102.2, Q102.3, R123.1
RECOVERY_KEY: R412.2, SW501.1
SOC_CON_RX: J503.3, U401.73
SOC_CON_TX: J503.2, U401.72
SOC_LT_RST: R213.1, U401.61
SOC_MCU_RST: R413.1, U401.90
SOC_NPOR: SW502.1, U401.74
SOC_RECOVERY: C410.1, R411.1, R412.1, U401.26
SPI_CS: U301.20, U401.101
SPI_MISO: U301.22, U401.98
SPI_MOSI: U301.23, U401.99
SPI_SCK: U301.21, U401.100
SS_RX1_N: J201.B10, U201.9, U202.5
SS_RX1_P: J201.B11, U201.8, U202.4
SS_RX2_N: J201.A10, U201.3, U203.5
SS_RX2_P: J201.A11, U201.2, U203.4
SS_TX1_N: J201.A3, U201.12, U202.2
SS_TX1_P: J201.A2, U201.11, U202.1
SS_TX2_N: J201.B3, U201.6, U203.2
SS_TX2_P: J201.B2, U201.5, U203.1
SWCLK: J501.3, U301.49
SWDIO: J501.2, U301.46
U102_BOOT: C107.1, U102.7
U102_EN: R111.2, R112.1, U102.3
U102_FB: R109.2, R110.1, U102.5
U102_SW: C107.2, L101.1, U102.8
U102_VCC: C106.1, U102.6
U103_BOOT: C115.1, U103.7
U103_EN: R115.2, R116.1, U103.3
U103_FB: R113.2, R114.1, U103.5
U103_SW: C115.2, L102.1, U103.8
U103_VCC: C114.1, U103.6
U104_EN: R117.2, U104.1
U104_FB: R118.2, R119.1, U104.5
U104_SW: L103.1, U104.3
U105_EN: C125.1, R120.2, U105.1
U105_FB: R121.2, R122.1, U105.5
U105_SW: L104.1, U105.3
VBUS_IN: F101.1, J101.A4, J101.A9, J101.B4, J101.B9
VCC_1V8_MOD: R411.2, U401.77
VCC_3V3_MOD: R201.2, R202.2, TP401.1, U401.78
VDDA_MCU: C308.1, C309.1, FB301.2, U301.13
VIN: C101.1, C103.1, C104.1, C105.1, C111.1, C112.1, C113.1, D101.1, F101.2, JP101.3, R101.1, R111.1, R115.1, R409.1, TP501.1, U102.2, U103.2
VIN_SENSE: C409.1, R409.2, R410.1, U401.27

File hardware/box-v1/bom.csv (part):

reference,qty,value,manufacturer,mpn,lcsc,lcsc_confidence,lcsc_evidence,jlc_type,assembly,dnp,unit_price_usd_est,price_basis,footprint,confidence,notes
C101,1,47uF 35V,KNSCHA,RVT47UF35V67RV0039,C2836440,Likely,search excerpt 2026-09-26,Extended (assumed),SMT,no,0.0190,search excerpt 2026-09-26,Capacitor_SMD:CP_Elec_6.3x7.7,Confirmed,"VIN bulk capacitor, damps ringing when a long cable is hot-plugged; aluminium electrolytic 47 µF 35 V ±20 %, 6.3x7.7 mm"
C102 C404,2,1uF 50V,Samsung Electro-Mechanics,CL10A105KB8NNNC,C15849,Likely,JLCPCB parts list snapshot 2026-04-02,Basic,SMT,no,0.0110,JLCPCB parts list snapshot 2026-04-02,Capacitor_SMD:C_0603_1608Metric,Confirmed,CH224K VDD capacitor; PC-side VBUS capacitor (UFP ≤ 10 µF); 50 V X5R 0603
C103 C104 C111 C112,4,10uF 50V X7R,Samsung Electro-Mechanics,CL31B106KBHNNNE,C89632,Likely,search excerpt 2026-09-26,Extended (assumed),SMT,no,0.0556,search excerpt 2026-09-26,Capacitor_SMD:C_1206_3216Metric,Confirmed,U102 input capacitor; U103 input capacitor; 50 V X7R 1206 (price: LCSC 100+ break)
C105 C113,2,100nF 50V,YAGEO,CC0603KRX7R9BB104,C14663,Likely,JLCPCB parts list snapshot 2026-04-02,Basic,SMT,no,0.0060,JLCPCB parts list snapshot 2026-04-02,Capacitor_SMD:C_0603_1608Metric,Confirmed,High-frequency capacitor at the U102 VIN/GND pins; High-frequency capacitor at the U103 VIN/GND pins; 50 V X7R 0603
C106 C114 C309,3,1uF 25V,Samsung Electro-Mechanics,CL05A105KA5NQNC,C52923,Likely,JLCPCB parts list snapshot 2026-04-02,Basic,SMT,no,0.0070,JLCPCB parts list snapshot 2026-04-02,Capacitor_SMD:C_0402_1005Metric,Confirmed,U102 internal LDO capacitor; U103 internal LDO capacitor; Extra VDDA capacitor for the ADC; 25 V X5R 0402
C107 C115 C120 C124 C125 C129 C203 C204 C205 C206 C207 C208 C209 C210 C211 C215 C218 C303 C304 C305 C306 C307 C308 C311 C402 C403 C405,27,100nF 16V / 100nF,Samsung Electro-Mechanics,CL05B104KO5NNNC,C1525,Likely,JLCPCB parts list snapshot 2026-04-02,Basic,SMT,no,0.0050,JLCPCB parts list snapshot 2026-04-02,Capacitor_SMD:C_0402_1005Metric,Confirmed,U102 bootstrap capacitor; U103 bootstrap capacitor; U104 high-frequency input capacitor; U105 high-frequency input capacitor; …; 16 V X7R 0402
C108 C109 C110 C116 C117 C118,6,22uF 25V X5R,Samsung Electro-Mechanics,CL31A226KAHNNNE,C12891,Likely,JLCPCB parts list snapshot 2026-04-02,Basic,SMT,no,0.0560,JLCPCB parts list snapshot 2026-04-02,Capacitor_SMD:C_1206_3216Metric,Confirmed,U102 output capacitor; U103 output capacitor; 25 V X5R 1206
C119 C123 C212 C213 C214 C310,6,10uF 10V,Samsung Electro-Mechanics,CL10A106KP8NNNC,C19702,Likely,JLCPCB parts list snapshot 2026-04-02,Basic,SMT,no,0.0110,JLCPCB parts list snapshot 2026-04-02,Capacitor_SMD:C_0603_1608Metric,Confirmed,U104 input capacitor; U105 input capacitor; 1V2 bulk capacitor at the LT7911D; 1V2_LT_A bulk capacitor; 3V3_LT bulk capacitor; 3V3 bulk capacitor at the MCU; 10 V X5R 0603
C121 C122 C126 C127 C401,5,22uF 25V X5R,Samsung Electro-Mechanics,CL21A226MAQNNNE,C45783,Likely,JLCPCB parts list snapshot 2026-04-02,Basic,SMT,no,0.0330,JLCPCB parts list snapshot 2026-04-02,Capacitor_SMD:C_0805_2012Metric,Confirmed,U104 output capacitor; U105 output capacitor; VCC5V0_SYS bulk capacitor next to the module; 25 V X5R 0805
C128,1,47nF 50V,Samsung Electro-Mechanics,CL10B473KB8NNNC,C1622,Likely,JLCPCB parts list snapshot 2026-04-02,Basic,SMT,no,0.0080,JLCPCB parts list snapshot 2026-04-02,Capacitor_SMD:C_0603_1608Metric,Confirmed,"Soft start (~0.5 ms), limits the charging current into the iPhone; 50 V X7R 0603"
C130 C312 C313,3,1nF,FH (Guangdong Fenghua),0402B102K500NT,C1523,Likely,JLCPCB parts list snapshot 2026-04-02,Basic,SMT,no,0.0050,JLCPCB parts list snapshot 2026-04-02,Capacitor_SMD:C_0402_1005Metric,Confirmed,U106 output filter before the ADC; CC1 ADC filter; CC2 ADC filter; 50 V X7R 0402
C201 C202,2,18pF C0G,FH (Guangdong Fenghua),0402CG180J500NT,C1549,Likely,JLCPCB parts list snapshot 2026-04-02,Basic,SMT,no,0.0040,JLCPCB parts list snapshot 2026-04-02,Capacitor_SMD:C_0402_1005Metric,Unknown,"[Unknown] Crystal load capacitor (unclear, per the Lontium reference design); Crystal load capacitor; 50 V C0G ±5 % 0402"
C216 C217,2,100nF,Samsung Electro-Mechanics,CL05B104KO5NNNC,C1525,Likely,JLCPCB parts list snapshot 2026-04-02,Basic,SMT,no,0.0050,JLCPCB parts list snapshot 2026-04-02,Capacitor_SMD:C_0402_1005Metric,Unknown,"[Unknown] AUX AC capacitor (direction/bias unclear, per the Lontium reference design); AUX AC capacitor; 16 V X7R 0402"
C219,1,10uF 25V,Samsung Electro-Mechanics,CL21A106KAYNNNE,C15850,Likely,JLCPCB parts list snapshot 2026-04-02,Basic,SMT,no,0.0230,JLCPCB parts list snapshot 2026-04-02,Capacitor_SMD:C_0805_2012Metric,Confirmed,iPhone-side VBUS capacitor (Type-C source ≤ 120 µF); 25 V X5R 0805
C220,1,100nF 50V,Samsung Electro-Mechanics,CL05B104KB54PNC,C307331,Likely,JLCPCB parts list snapshot 2026-04-02,Basic,SMT,no,0.0070,JLCPCB parts list snapshot 2026-04-02,Capacitor_SMD:C_0402_1005Metric,Confirmed,iPhone VBUS high-frequency capacitor; 50 V X7R 0402
C301 C302,2,18pF C0G,FH (Guangdong Fenghua),0402CG180J500NT,C1549,Likely,JLCPCB parts list snapshot 2026-04-02,Basic,SMT,no,0.0040,JLCPCB parts list snapshot 2026-04-02,Capacitor_SMD:C_0402_1005Metric,Confirmed,HSE load capacitor: 2 x (12 pF - ~3 pF stray); HSE load capacitor; 50 V C0G ±5 % 0402
C314 C406 C407 C409,4,10nF / 10nF 50V,Samsung Electro-Mechanics,CL05B103KB5NNNC,C15195,Likely,JLCPCB parts list snapshot 2026-04-02,Basic,SMT,no,0.0050,JLCPCB parts list snapshot 2026-04-02,Capacitor_SMD:C_0402_1005Metric,Confirmed,VBUS ADC filter; TX centre-tap capacitor (voltage-mode PHY); RX centre-tap capacitor; VIN ADC filter; 50 V X7R 0402
C408,1,1nF 2kV X7R,FH (Guangdong Fenghua),1206B102K202NT,C9196,Likely,JLCPCB parts list snapshot 2026-04-02,Basic,SMT,no,0.0120,JLCPCB parts list snapshot 2026-04-02,Capacitor_SMD:C_1206_3216Metric,Confirmed,Bob-Smith node capacitor (2 kV keeps the 1500 V isolation of the magnetics); 2 kV X7R 1206
C410,1,1nF C0G,Murata,GRM1555C1H102JA01D,C76947,Likely,search excerpt 2026-09-26,Extended (assumed),SMT,no,0.0100,allowance (no price found),Capacitor_SMD:C_0402_1005Metric,Confirmed,RECOVERY key filter; 50 V C0G 0402
D101,1,SMBJ20A,hongjiacheng,SMBJ20A,C19077575,Likely,JLCPCB parts list snapshot 2026-04-02,Preferred,SMT,no,0.0350,JLCPCB parts list snapshot 2026-04-02,Diode_SMD:D_SMB,Confirmed,"TVS on VIN: 20 V standoff, 32.4 V clamp, below the 36 V input rating of the LMR33630; 600 W TVS, 20 V standoff, 32.4 V clamp at 18.5 A, SMB"
D102,1,BZT52C10,Diodes Incorporated,BZT52C10-7-F,C155227,Likely,search excerpt 2026-09-26,Extended (assumed),SMT,no,0.0200,allowance (no price found),Diode_SMD:D_SOD-123,Confirmed,10 V zener clamping Vgs in Option B (VIN up to 20 V); 10 V 500 mW zener SOD-123
D104,1,SS34,MDD (Microdiode Electronics),SS34,C8678,Likely,JLCPCB parts list snapshot 2026-04-02,Basic,SMT,no,0.0310,JLCPCB parts list snapshot 2026-04-02,Diode_SMD:D_SMA,Confirmed,3 A 40 V Schottky: PC_VBUS -> 5V_SYS (development mode); 3 A 40 V Schottky SMA
D201 D401,2,SMF6.0A,Littelfuse,SMF6.0A,C207260,Likely,search excerpt 2026-09-26,Extended (assumed),SMT,no,0.0500,allowance (no price found),Diode_SMD:D_SOD-123F,Confirmed,"iPhone VBUS TVS (Option B with VIN up to 20 V: change to SMF22A); PC VBUS TVS; 200 W unidirectional TVS, 6 V standoff, SOD-123FL"
D501,1,RED,Hubei KENTO Elec,KT-0603R,C2286,Likely,JLCPCB parts list snapshot 2026-04-02,Basic,SMT,no,0.0090,JLCPCB parts list snapshot 2026-04-02,LED_SMD:LED_0603_1608Metric,Confirmed,"RED status LED (red: no iPhone, yellow: HID but no video, green: ready); red 615-630 nm, Vf 1.8-2.4 V @ 20 mA"
D502,1,YELLOW,Foshan NationStar,NCD0603Y2,C89811,Likely,JLCPCB parts list snapshot 2026-04-02,Preferred,SMT,no,0.0210,JLCPCB parts list snapshot 2026-04-02,LED_SMD:LED_0603_1608Metric,Confirmed,"YELLOW status LED (red: no iPhone, yellow: HID but no video, green: ready); yellow 586-595 nm, Vf 1.6-2.6 V"
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

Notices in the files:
hardware/box-v1/README.md:
- Footprint of the HRO TYPE-C-31-M-04 (public domain, Unlicense): https://github.com/jenschr/USB-C-Connectors
parts and their libraries:
Korean Hroparts TYPE-C-31-M-04 USB-C 24P receptacle, right angle, hybrid: A row SMD, B row through-hole (LCSC C129018). From github.com/jenschr/USB-C-Connectors, public domain (Unlicense), built and tested by its author
